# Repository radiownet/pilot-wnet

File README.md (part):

# Pilot Wnet

**An open studio controller for radio: arcade buttons and a joystick on an ESP32-S3 board designed to talk USB HID, Ethernet and Bluetooth LE (firmware not yet run on hardware) and to double as a LoRa 868 MHz mesh node (draft firmware variants).**

Polski: [README.pl.md](README.pl.md)

> [!WARNING]
> **Rev A is a prototype. DO NOT ORDER the Rev A board.**
> The layout has known defects (see [Known issues in Rev A](#known-issues-in-rev-a)) and needs a re-layout (Rev B) before anyone manufactures it.

> [!IMPORTANT]
> **AI-generated design, not reviewed by an engineer.** The Rev A schematic and PCB layout were generated by Python scripts (using SKiDL, Freerouting and a custom router) that AI agents (Claude) wrote and ran. ERC and DRC report 0 errors, but no hardware engineer has reviewed the design. See [How this project was made](#how-this-project-was-made).

*Render, **not a photograph**: the Rev A board has not been manufactured. An AI agent (Claude) made it in Blender (Cycles) from the KiCad files in this repository. The USB-C and RJ45 sockets and the tactile switches are approximate models, part markings are simplified, and parts marked DNP are not shown. More views: [top](docs/img/pilot-wnet-rev-a-render-top.jpg), [ESP32-S3 module close-up](docs/img/pilot-wnet-rev-a-render-esp32.jpg).*

## What is Pilot Wnet

Pilot Wnet is a physical controller for a radio studio. It was developed at the Polish radio station Radio Wnet (Radio Wnet Sp. z o.o.) and is published as open hardware. The operator presses big arcade buttons or moves a joystick; the controller sends authenticated state frames to the studio computer, where host software turns them into actions.

- **Controls:** six arcade buttons (four colour buttons, START and STOP) and a four-way arcade joystick in a wooden bartop-style cabinet; a Qwiic connector for an I2C OLED display.
- **Links to the studio computer (as designed):** USB HID, Ethernet (UDP) and Bluetooth LE. Wi-Fi is available but off by default. Every frame carries a CRC-16 and a truncated HMAC-SHA256 bound to a per-session nonce from the host. The frame and session protocol is documented in [docs/ESP32_PROTOKOL.md](docs/ESP32_PROTOKOL.md) (Polish).
- **Mesh node:** the same board carries an Ebyte E22-900M22S LoRa module (868 MHz) and can be flashed as a node for Meshtastic®- or MeshCore-based mesh networks (draft firmware variants, not built yet).

**There is no public host application.** Over USB the controller is a vendor-defined HID device (usage page `0xFF00`) that sends HMAC-authenticated frames, so you need your own host software to use it; the protocol document above is the reference. The host implementation (an application for the studio computer) is not public (yet); it currently reads USB HID and UDP, and BLE exists only in the firmware.

### Hardware at a glance (Rev A)

| Block | Rev A |
|---|---|
| Board | 90 × 100 mm, 4 layers (F.Cu signals, In1 GND, In2 +3V3, B.Cu signals), FR-4 1.6 mm, all parts on the top side, KiCad 10 |
| MCU | ESP32-S3-WROOM-1-N16R8 (16 MB flash, 8 MB octal PSRAM). The module is flush with the top edge; its PCB antenna lies over the board with a copper keep-out on all four layers (Espressif recommends the antenna beyond the edge or a cut-out; to be considered in Rev B) |
| Ethernet | WIZnet W5500 with a 25 MHz crystal, RJ45 HR911105A with integrated magnetics (the W5500 has no auto-MDIX) |
| Power | USB-C 5 V only (fuse, TVS, USBLC6), TI TLV62569 buck converter 5 V → 3.3 V; no battery in Rev A |
| LoRa | Ebyte E22-900M22S (SX1262, TCXO), 868 MHz, soldered by hand (not assembled by the factory), antenna through the module's IPEX connector |
| Inputs | 6 × JST XH 4-pin for buttons (J10–J15: signal, GND, LED+ 5 V, LED−), JST XH 5-pin for the joystick (J16); RC filters and SRV05-4 ESD arrays |
| Other | Qwiic for the OLED (J17) and for applications (J18), expansion header (J19), service UART (J20), RESET and BOOT buttons, status LED |
| Not assembled (DNP) | button backlight driver (PCA9685 + 6 × AO3400A), the E22 module, option resistors, USB capacitors, the buck converter feed-forward capacitor |
| Assembly | about 128 placed parts, 43 BOM lines with LCSC part numbers (JLCPCB assembly) |

Design decisions and their reasons: [DECYZJE.md](DECYZJE.md) (Polish, D1–D11). Some of its entries are out of date: the reason given for D7 ("solid ground") and the "Consequences" section (enclosure sized for the board) contradict the current files, see [docs/AUDYT_REV_A.md](docs/AUDYT_REV_A.md).

## Status

| Part | State |
|---|---|
| Schematic | generated from `pcb/obwod.py` by `pcb/schemat.py`; ERC 0 errors, 6 warnings (`lib_symbol_mismatch`: flattened derived symbols, no effect on connectivity) |
| PCB layout Rev A | DRC 0 errors, 0 unconnected items, 0 schematic-parity issues, 21 warnings (`lib_footprint_mismatch`: solder paste removed from DNP pads on purpose); **known layout defects, DO NOT ORDER** |
| Firmware (MicroPython) | written and tested in CPython against mocks; **never run on a real board** |
| Meshtastic / MeshCore variants | draft variant files, not built |
| Enclosure | parametric generators for cutting sheets and a 3D model; **does not match the Rev A board yet** (outline, USB-C/RJ45/SMA cut-outs, rear-wall pocket D8); some part dimensions are working values until real parts are measured |
| Circuit simulations | ngspice tests of the analogue sub-circuits (`sim/`); five expected failures document requirements that Rev A does not meet |
| Radio compliance (RED/CE) | **not assessed** |

ERC/DRC figures come from KiCad 10.0.8 on 20 November 2026 (`pcb/wyniki/erc.json`, `pcb/wyniki/drc.json`).

## Known issues in Rev A

An AI-agent audit (Claude agents, 20 Nov 2026, measurements taken from the board file; not reviewed by an engineer) found the defects below. They are the reason for Rev B: see the [Re-layout Rev B](.github/ISSUE_TEMPLATE/relayout-rev-b.md) task. The finding IDs refer to the audit summary in [docs/AUDYT_REV_A.md](docs/AUDYT_REV_A.md) (Polish, with an English summary).

1. **Inner planes carry signals** (layout-01, zasilanie-15). Most signals run on the inner layers (In1 GND, In2 +3V3), while B.Cu is almost empty. Under the W5500 the In1 ground covers only 39% of the package outline.
2. **Buck converter (U3, TLV62569) placed against the TI datasheet** (zasilanie-01, layout-02). The input capacitor is far from the IC, the SW node is long, and the FB trace runs under the SW node.
3. **25 MHz crystal (Y1): bad XO routing** (layout-04). The XO trace from the W5500 to Y1 makes a 17.6 mm detour through 4 vias (via R58 and C41) and runs on In2 directly under the crystal; LoRa SPI traces run on In1 under it. XI (5.1 mm) is fine.
4. **ESD protection far from the connectors** (zasilanie-02, interfejsy-04). For 6 of the 10 inputs the SRV05-4 channel is 46–66 mm (straight line) from its connector, because channels follow list order, not placement; the input traces are up to 93 mm long, mostly on In1.
5. **Ethernet pairs** (layout-05, interfejsy-05). The traces from the W5500 to the RJ45 are not routed as differential pairs over continuous ground: the halves of a pair run on different layers, with length mismatches of 11 mm and 4.6 mm.

Other open points (more in [docs/AUDYT_REV_A.md](docs/AUDYT_REV_A.md)):

- The crystal load capacitors (2 × 18 pF) are probably too small for a crystal with CL = 18 pF, so the oscillator may run fast (interfejsy-09). Simulation results and options: [sim/README.md](sim/README.md) (Polish).
- The W5500 reset RC has a small margin when 3V3 rises slowly (same file); the W5500 is reset only by this RC, not by the ESP32 (interfejsy-14).
- J19 (expansion) and J20 (service UART) are both 1 × 6 headers with **swapped power pins** (J19: pin 1 = +3V3, pin 2 = GND; J20: pin 1 = GND, pin 2 = +3V3). A UART adapter plugged into the wrong header swaps power and ground (interfejsy-03).
- **J20 does not match a standard 6-pin FTDI cable**: in either orientation the cable's VCC (+5 V) lands on EN or IO0 (interfejsy-02).
- **Pin 3 of every button connector J10–J15 always carries +5 V**, although the LED driver is not fitted; a miswired harness feeds 5 V through the SRV05-4 into the 3V3 rail (produkt-15, interfejsy-06).
- **D1 (SMF5.0A, breakdown 6.4–7.0 V) does not protect U3**, whose input is rated at 6 V maximum (zasilanie-04).
- USB D+/D− are not routed as a pair and the ESD path on D− is a stub (layout-06).
- The input of U7 (74LVC1G04) floats while the E22 module is not fitted (zasilanie-06, interfejsy-07).
- The USB-C footprint (J1) should be double-checked against the connector datasheet.
- The firmware uses MicroPython's built-in USB VID/PID; the project has no VID/PID of its own.

## How this project was made

Pilot Wnet is an experiment in agentic hardware design, and we label it as such.

- The circuit is described in Python with SKiDL 3.0 (`pcb/obwod.py`). A custom generator writes the KiCad schematic from it (`pcb/schemat.py`, net labels instead of wires).
- Placement, ground zones and net classes are scripted with KiCad's Python API (`pcb/plytka.py`). Routing was done with Freerouting 2.5.0, and the last connections were closed by a custom raster router (`pcb/v01/`).
- These scripts, the MicroPython firmware and its tests, the SPICE tests, the enclosure and Blender generators, the research reports (`research/`), the decision register, the ordering notes, the audit summary and this documentation were written by AI agents (Claude, by Anthropic) working under human direction. Decisions marked as defaults wait for approval by the project team.
- The result passes ERC and DRC with 0 errors. **No hardware engineer has reviewed the schematic or the layout yet**, and the audit above shows that 0 DRC errors does not make a good board.

For Rev B we want people to take over: a re-layout by a human designer, review by others, and automatic ERC/DRC checks on every change.

## Repository layout

| Path | Contents |
|---|---|
| `pcb/kicad/` | KiCad 10 project: schematic, board, design rules, netlist, library tables |
| `pcb/lib/` | project library (symbols and footprints; the E22 3D model is not included) |
| `pcb/*.py`, `pcb/v01/` | generator and check scripts: SKiDL circuit, schematic generator, placement, routing, fabrication export (notes in Polish: `pcb/README.md`, `pcb/v01/README_v01.md`) |
| `pcb/wyniki/` | ERC and DRC reports (JSON) |
| `firmware/micropython/` | controller firmware in MicroPython and its CPython tests (`testy/`) |
| `firmware/meshtastic/`, `firmware/meshcore/` | draft mesh-node variants (not built); `firmware/ci/build-mesh.yml` is an inactive draft workflow |
| `sim/` | ngspice tests of analogue sub-circuits, generated from `pcb/obwod.py` |
| `projekt/` | `arcade.toml` (enclosure and part dimensions; still assumes an older 100 × 100 mm board, see [Status](#status)) and the cutting-sheet generator (SVG for laser/CNC) |
| `blender/` | generator of the 3D model and renders of the cabinet (Blender batch mode; outputs and the top-panel artwork are not included) |
| `zamowienie/` | ordering notes for Rev A (reference only: do not order Rev A) |
| `research/` | research reports R1, R2, R3 and R5 (Polish, AI-written, sources with check dates; R4 is not included) |
| `docs/` | frame and session protocol (`ESP32_PROTOKOL.md`), hardware overview (`SPRZET.md`), audit summary (`AUDYT_REV_A.md`), all in Polish; renders of the Rev A board (`img/`) |
| `DECYZJE.md` | decision register D1–D11 (Polish) |
| `LICENSES/`, `REUSE.toml`, `NOTICE.md` | licence texts, per-file licensing (REUSE) and third-party notices |
| `.github/` | CI workflows, pull request and issue templates |

## Reproduce and verify

### ERC and DRC (KiCad 10)

The board and project files are saved with KiCad 10.0.8; the schematic is written by `pcb/schemat.py` in an older file format, which KiCad 10 opens and converts on save (expect a large one-time diff). From `pcb/kicad/`:

```sh
kicad-cli sch erc --severity-all --format json -o ../wyniki/erc.json pilot_wnet.kicad_sch
kicad-cli pcb drc --schematic-parity --refill-zones --severity-all --format json -o ../wyniki/drc.json pilot_wnet.kicad_pcb
```

Expected: 0 errors in both reports, 0 unconnected items, 0 schematic-parity issues, and the warnings listed under [Status](#status). CI runs the same checks in the official `kicad/kicad:10.0.8` Docker image on every push to main and every pull request ([.github/workflows/kicad.yml](.github/workflows/kicad.yml)) and keeps the reports as build artefacts. The gate is **0 errors, 0 unconnected items and 0 schematic-parity issues**; other warnings are checked in review.

Do not run "Update footprints from library" on the DNP parts: it restores the solder paste that was removed on purpose.

### Firmware tests (no hardware needed)

CPython 3.11 or newer, standard library only; MicroPython modules are replaced by mocks (`testy/atrapy.py`). Run each test file on its own, from `firmware/micropython/`:

```sh
for t in testy/test_*.py; do python -I -B -X utf8 "$t" || echo "FAILED: $t"; done
```

Windows (cmd): `for %f in (testy\test_*.py) do python -I -B -X utf8 %f`

The mocks show only that the code calls the APIs with the right pins and arguments. They do not show that USB HID, the W5500 or the SX1262 behave that way on a real board. A few tests are skipped on purpose: they document open findings. CI: [.github/workflows/firmware.yml](.github/workflows/firmware.yml).

### Circuit simulations (optional)

From `sim/`: `python -I -B -X utf8 -m unittest discover -s . -p "test_*.py"`. Without ngspice only the calculation and topology tests run. The SPICE tests need the ngspice console binary (set `PILOT_NGSPICE` to its path) and the `spicelib` package from PyPI, which brings NumPy and SciPy.

### Regenerating the board from scripts

The generator chain is published for transparency, but it is not a turnkey build yet. It needs KiCad 10's Python, SKiDL 3.0 and Freerouting 2.5.0 on a Java runtime, and parts of it still assume the original authors' setup. Re-running `pcb/plytka.py` overwrites manual copper edits.

### Dependencies

| Task | Needs |
|---|---|
| Firmware tests | CPython ≥ 3.11, standard library only |
| Firmware on the board | MicroPython for ESP32-S3 and the micropython-lib packages `usb-device-hid`, `aioble`, `lora-sync`, `lora-sx126x` (installed with `mpremote mip install`, see `firmware/README.md`) |
| ERC/DRC | KiCad 10 (`kicad-cli`) |
| Board generator (`pcb/`) | KiCad 10 Python (`pcbnew`), SKiDL 3.0, Freerouting 2.5.0 with a Java runtime, KiKit 1.8.1 (`pcb/fab.py`), NumPy (`pcb/v01/` router), PyMuPDF (`pcb/v01/opis_pdf.py`) |
| Simulations (`sim/`) | ngspice (console binary), `spicelib` (with NumPy, SciPy) |
| Enclosure (`projekt/`, `blender/`) | Python ≥ 3.11 (`tomllib`); Blender in batch mode for `blender/` |
| Licence check | `reuse` (REUSE tool) |

## Licences

| Scope | Licence |
|---|---|
| Hardware design: KiCad project and project library (`pcb/`), including the scripts that generate the design and their CSV/JSON data; enclosure and part geometry and the cutting-sheet generator (`projekt/`) | [CERN-OHL-S-2.0](LICENSES/CERN-OHL-S-2.0.txt) |
| Software: MicroPython firmware and tests (`firmware/micropython/`), MeshCore helper files (`firmware/meshcore/`), the draft mesh CI (`firmware/ci/`), simulations (`sim/`), the Blender generator (`blender/`), CI workflows | [MIT](LICENSES/MIT.txt) |
| Documentation: README files, `docs/`, `research/`, `DECYZJE.md`, `zamowienie/`, CONTRIBUTING, NOTICE, GitHub templates | [CC-BY-SA-4.0](LICENSES/CC-BY-SA-4.0.txt) |
| `.gitignore` files | [CC0-1.0](LICENSES/CC0-1.0.txt) |

Exceptions:

- `firmware/meshtastic/` is a derivative of the Meshtastic firmware and is licensed under the GPL ([GPL-3.0-only](LICENSES/GPL-3.0-only.txt)), like upstream.
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
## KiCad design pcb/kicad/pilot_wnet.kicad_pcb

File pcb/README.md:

# Pilot Wnet Rev A — płytka (KiCad 10, tor agentowy „kod → KiCad”)

> Projekt przygotował agent SI (Claude) w torze dla inżynierów pracujących agentowo. Każdy krok jest skryptem,
> a wynik to zwykły projekt KiCada 10, który człowiek otwiera i poprawia w GUI. Decyzje: `../DECYZJE.md`.
> Architektura i źródła liczb: `../research/R3_architektura_elektroniki.md` oraz wyciągi z kart producentów
> (workflow 18.10.2026: W5500 + HR911105A wg referencji WIZnet, ESP32-S3-WROOM-1 v1.8 + HDG, Ebyte E22,
> TI TLV62569, biblioteka JLCPCB).

## Tor narzędzi

| Krok | Skrypt | Narzędzie | Wynik |
|---|---|---|---|
| 1. Obwód (źródło prawdy) | `obwod.py` | SKiDL 3.0 | `kicad/pilot_wnet.net`, `kicad/bom_obwod.csv` |
| 2. Schemat | `schemat.py` | własny generator (etykiety sieci, bez przewodów) | `kicad/pilot_wnet.kicad_sch` — ERC: 0 błędów |
| 3. Płytka: obrys, rozmieszczenie, strefy GND, klasy sieci | `plytka.py uloz` | pcbnew (KiCad 10.0.1) | `kicad/pilot_wnet.kicad_pcb`, `.dsn` (plik pośredni, poza repozytorium) |
| 4. Trasowanie | `plytka.py trasuj` | Freerouting 2.5.0 (JAR, JRE 25, `-da`) | ścieżki z `.ses` (plik pośredni, poza repozytorium) |
| 5. Zgodność ze schematem, wykończenie | `plytka.py sciezki`, `plytka.py wykoncz` | pcbnew | ścieżki footprintów = UUID symboli; poszerzenie przewężeń, przelotki zszywające GND, reguły DRU |
| 6. DRC, panel KiKit, pliki JLCPCB, 3D (tor historyczny Rev A z 18.10 — niżej) | `fab.py` | kicad-cli, KiKit 1.8.1 | `wyniki/drc.json`, `kicad/pilot_wnet_panel.kicad_pcb` (poza repozytorium), `wyniki/jlcpcb/`, `wyniki/3d/` |

Kroki 1–6 to tor Rev A z 18.10.2026. Płytka w `kicad/` jest wersją v0.1 (zamówieniową): powstała z wyniku tego toru
dodatkowymi krokami z `v01/README_v01.md` (dotrasowanie, domknięcie, ręczne usunięcie wiszących przelotek, poprawki
opisu i poprawki przed zamówieniem). Panel KiKit 100 × 100 mm z kroku 6 jest torem historycznym (panel z 18.10 miał
starą trasę i nie jest częścią repozytorium) — pliki zamówienia v0.1 robią `v01/eksport_v01.py`
i `v01/pakiet_zamowienie_v01.py` (instrukcja: `../zamowienie/README.md`).

## Uruchamianie

Tor nie zależy od konkretnej maszyny. Potrzebne:

- KiCad 10 (Python KiCada z modułem `pcbnew` i `kicad-cli`); Rev A powstała w 10.0.1, poprawki przed zamówieniem v0.1
  (20.11) w 10.0.8;
- venv z dostępem do `pcbnew`: SKiDL 3.0 (`obwod.py`), KiKit 1.8.1 (tylko `fab.py`), easyeda2kicad (tylko do pobierania
  części z biblioteki EasyEDA/LCSC);
- do `plytka.py trasuj`: Java (JRE) 25 i Freerouting 2.5.0 jako JAR (tor Rev A z 18.10 wskazywał JRE jdk-25.0.4.1+1,
  dotrasowanie v0.1 z 19.11 użyło Temurin JRE 25.0.5+8).

Ścieżki narzędzi ustawiasz zmiennymi środowiskowymi:

| Zmienna | Skrypty | Domyślnie |
|---|---|---|
| `KICAD_CLI` | `cli.py`, `fab.py`, `v01/eksport_v01.py` | `C:\Program Files\KiCad\10.0\bin\kicad-cli.exe`; w `eksport_v01.py` instalacja dla użytkownika `%LOCALAPPDATA%\Programs\KiCad\10.0\bin\kicad-cli.exe` |
| `KICAD10_SYMBOL_DIR` | `obwod.py`, `schemat.py` | `C:\Program Files\KiCad\10.0\share\kicad\symbols` |
| `KICAD10_FOOTPRINT_DIR` | `obwod.py`, `plytka.py`, `sonda_fp.py` | `C:\Program Files\KiCad\10.0\share\kicad\footprints` |
| `KICAD10_3DMODEL_DIR` | KiCad (modele 3D footprintów z biblioteki KiCada); `eksport_v01.py` ustawia ją sam | — |
| `PILOT_JAVA` | `plytka.py trasuj` | `java` z `PATH` |
| `FREEROUTING` | `plytka.py trasuj` | `pcb/narzedzia/freerouting-2.5.0.jar` (katalog `narzedzia/` jest w `.gitignore`) |

Przy KiCadzie zainstalowanym gdzie indziej (instalacja dla użytkownika, Linux, macOS) ustaw zmienne KiCada jawnie.

**UWAGA: każdy krok łańcucha nadpisuje pliki w `kicad/`.** `obwod.py --wyjscie kicad` nadpisuje `pilot_wnet.net`
i `bom_obwod.csv`; `schemat.py` — `pilot_wnet.kicad_sch`, `piny_nc.json` i `sym-lib-table`; `plytka.py uloz`, `trasuj`,
`sciezki` i `wykoncz` — płytkę (`uloz` także `fp-lib-table`, `wykoncz` — `pilot_wnet.kicad_dru`). Uruchomienie łańcucha
w `kicad/` zniszczy płytkę v0.1 (zamówieniową), która powstała dodatkowym torem z `v01/README_v01.md`. Do eksperymentów
używaj osobnego katalogu **obok `lib/`** (np. `kicad_proba/`, jest w `.gitignore`): tabele bibliotek i model 3D E22
wskazują `${KIPRJMOD}/../lib`, a `plytka.py uloz` czyta `piny_nc.json` z katalogu wyjściowego i bez niego DRC zgłosi
niezgodność ze schematem. `schemat.py --wyjscie` przyjmuje ścieżkę pliku, nie katalogu.

Z katalogu `pcb/`, Pythonem KiCada (venv jak wyżej):

```bash
python obwod.py --wyjscie kicad_proba && python schemat.py --netlista kicad_proba/pilot_wnet.net --wyjscie kicad_proba/pilot_wnet.kicad_sch && python plytka.py uloz --netlista kicad_proba/pilot_wnet.net --wyjscie kicad_proba && python plytka.py trasuj --wyjscie kicad_proba --przebiegi 15 && python plytka.py sciezki --wyjscie kicad_proba && python plytka.py wykoncz --wyjscie kicad_proba
```

`fab.py` nie ma parametrów i działa zawsze na `kicad/`: nadpisuje `wyniki/drc.json` (raport płytki v0.1 w repozytorium)
i tworzy panel `kicad/pilot_wnet_panel.*` (w `.gitignore`). Freerouting z `-mt 8` nie jest deterministyczny, więc łańcuch
nie odtworzy płytki bajt w bajt; stanem odniesienia jest `kicad/pilot_wnet.kicad_pcb` w tym repozytorium.

Model 3D modułu E22 (`lib/pilot_jlc.3dshapes/WIRELM-SMD_L20.0-W14.0-H3.0-E22-900M22S.step`, z biblioteki EasyEDA/LCSC
przez easyeda2kicad) **nie jest dołączony** — jego licencja jest nieustalona. Footprint i płytka nadal go wskazują, więc
podgląd 3D, rendery i eksport STEP/GLB (`fab.py`) pokażą moduł E22 bez bryły (KiCad może zgłosić brak modelu); miedzi,
Gerberów ani BOM to nie zmienia.

## Płytka

- 90 × 100 mm, 4 warstwy (In1 GND, In2 +3V3), FR-4 1,6 mm; w torze Rev A z 18.10 panel 100 × 100 mm z listwami 5 mm po bokach (KiKit, `fab.py`) — tor historyczny, zamówienie v0.1: `v01/eksport_v01.py` i `../zamowienie/README.md`.
- Tylna krawędź (y = 0) przy tylnej ściance obudowy: USB-C (J1), RJ45 z transformatorem (J2), antena PCB modułu ESP32-S3-WROOM-1 (strefa bez miedzi z footprintu), dioda stanu D2.
- Przednia krawędź: złącza 6 przycisków JST XH 4-pin (J10–J15: 1 sygnał, 2 GND, 3 LED+ 5 V, 4 LED−); lewa: joystick XH 5-pin (J16: 1 GND, 2 góra, 3 dół, 4 lewo, 5 prawo). Prawa: Qwiic OLED (J17) i Qwiic aplikacji (J18), rozszerzenia (J19), serwis UART (J20), RESET i BOOT.
- Przydział GPIO: tabela w `obwod.py` i `../firmware/micropython/lib/konfig_plytki.py` (zgodne, sprawdzone przez recenzenta firmware).
- Bez montażu (DNP): tor podświetlenia (PCA9685, 6 × AO3400A — D1), moduł E22 (lutowany ręcznie — D4), rezystory opcji, kondensatory USB, feed-forward przetwornicy.

## Znane ograniczenia i decyzje techniczne

- **schematizer 0.2.0** (SKiDL) zwierał sieci (ERC: +3V3 z GND) i zapisywał symbol HR911105A nieczytelny dla KiCada 10.0.1 — zastąpiony `schemat.py`.
- **Freerouting CLI 2.5.0 (natywny)** wywraca się w pętli trasowania (GraalVM: brak konfiguracji serializacji `ComponentOutline`) i wisi — używamy JAR na JRE 25.
- Footprint WROOM-1 ma zawężony obrys montażowy (biblioteczny obejmował 15 mm wokół anteny; strefę RF pilnuje strefa bez miedzi) i przelotki termiczne 0,3 mm (min. JLCPCB dla 2 warstw) — stąd ostrzeżenie `lib_footprint_mismatch`.
- Symbol E22 z easyeda2kicad (C411293) ma ręcznie nadane typy pinów wg karty Ebyte.
- Antena LoRa przez złącze IPEX na module (bez ścieżki RF 50 Ω na płytce bez kontroli impedancji).
- Ostrzeżenia ERC `lib_symbol_mismatch` (AO3400A, TLV62569): spłaszczone symbole dziedziczące, bez wpływu na połączenia.

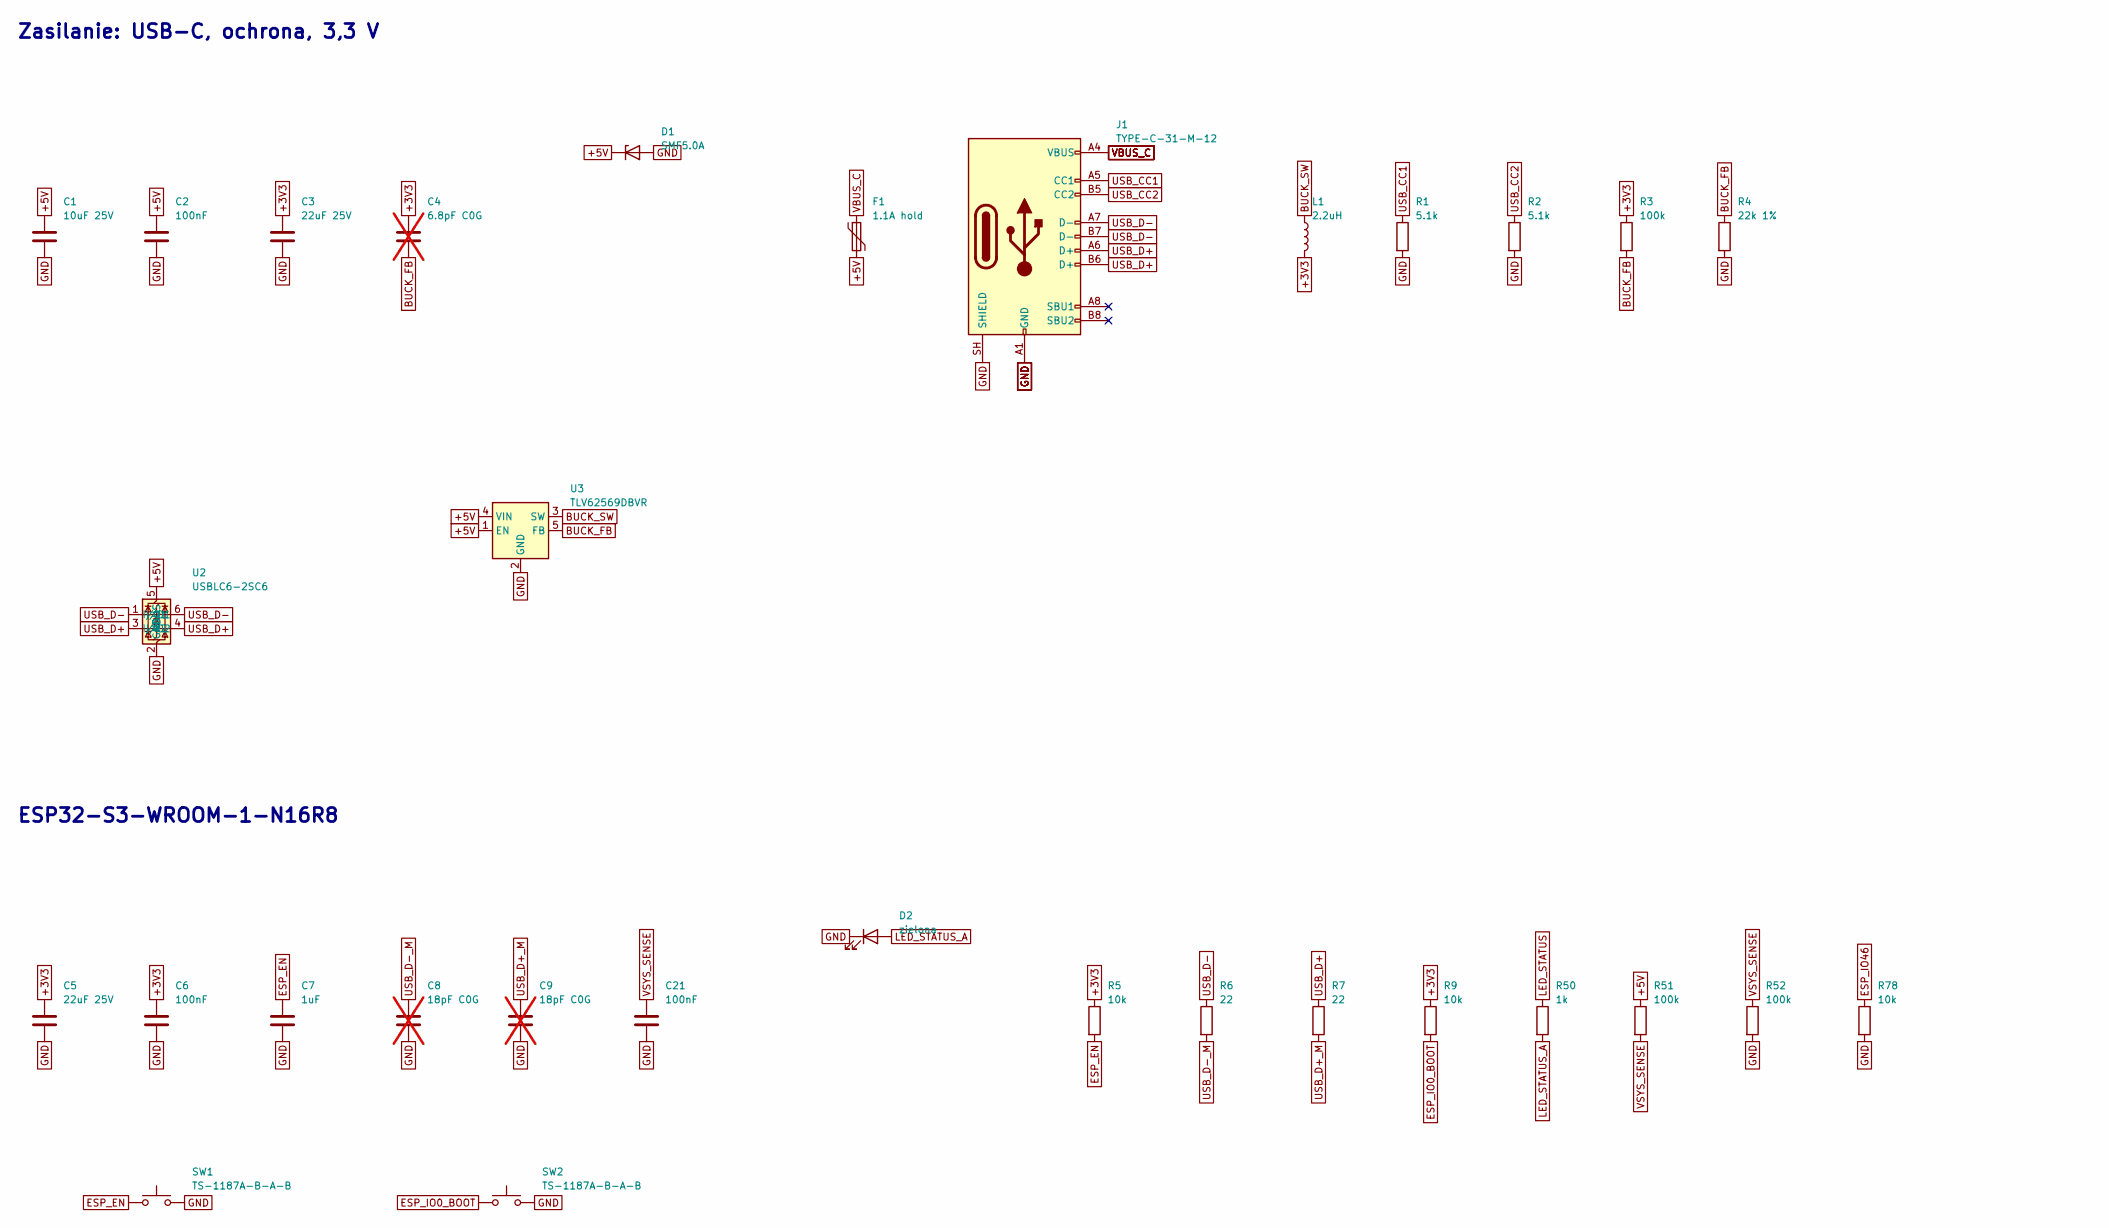
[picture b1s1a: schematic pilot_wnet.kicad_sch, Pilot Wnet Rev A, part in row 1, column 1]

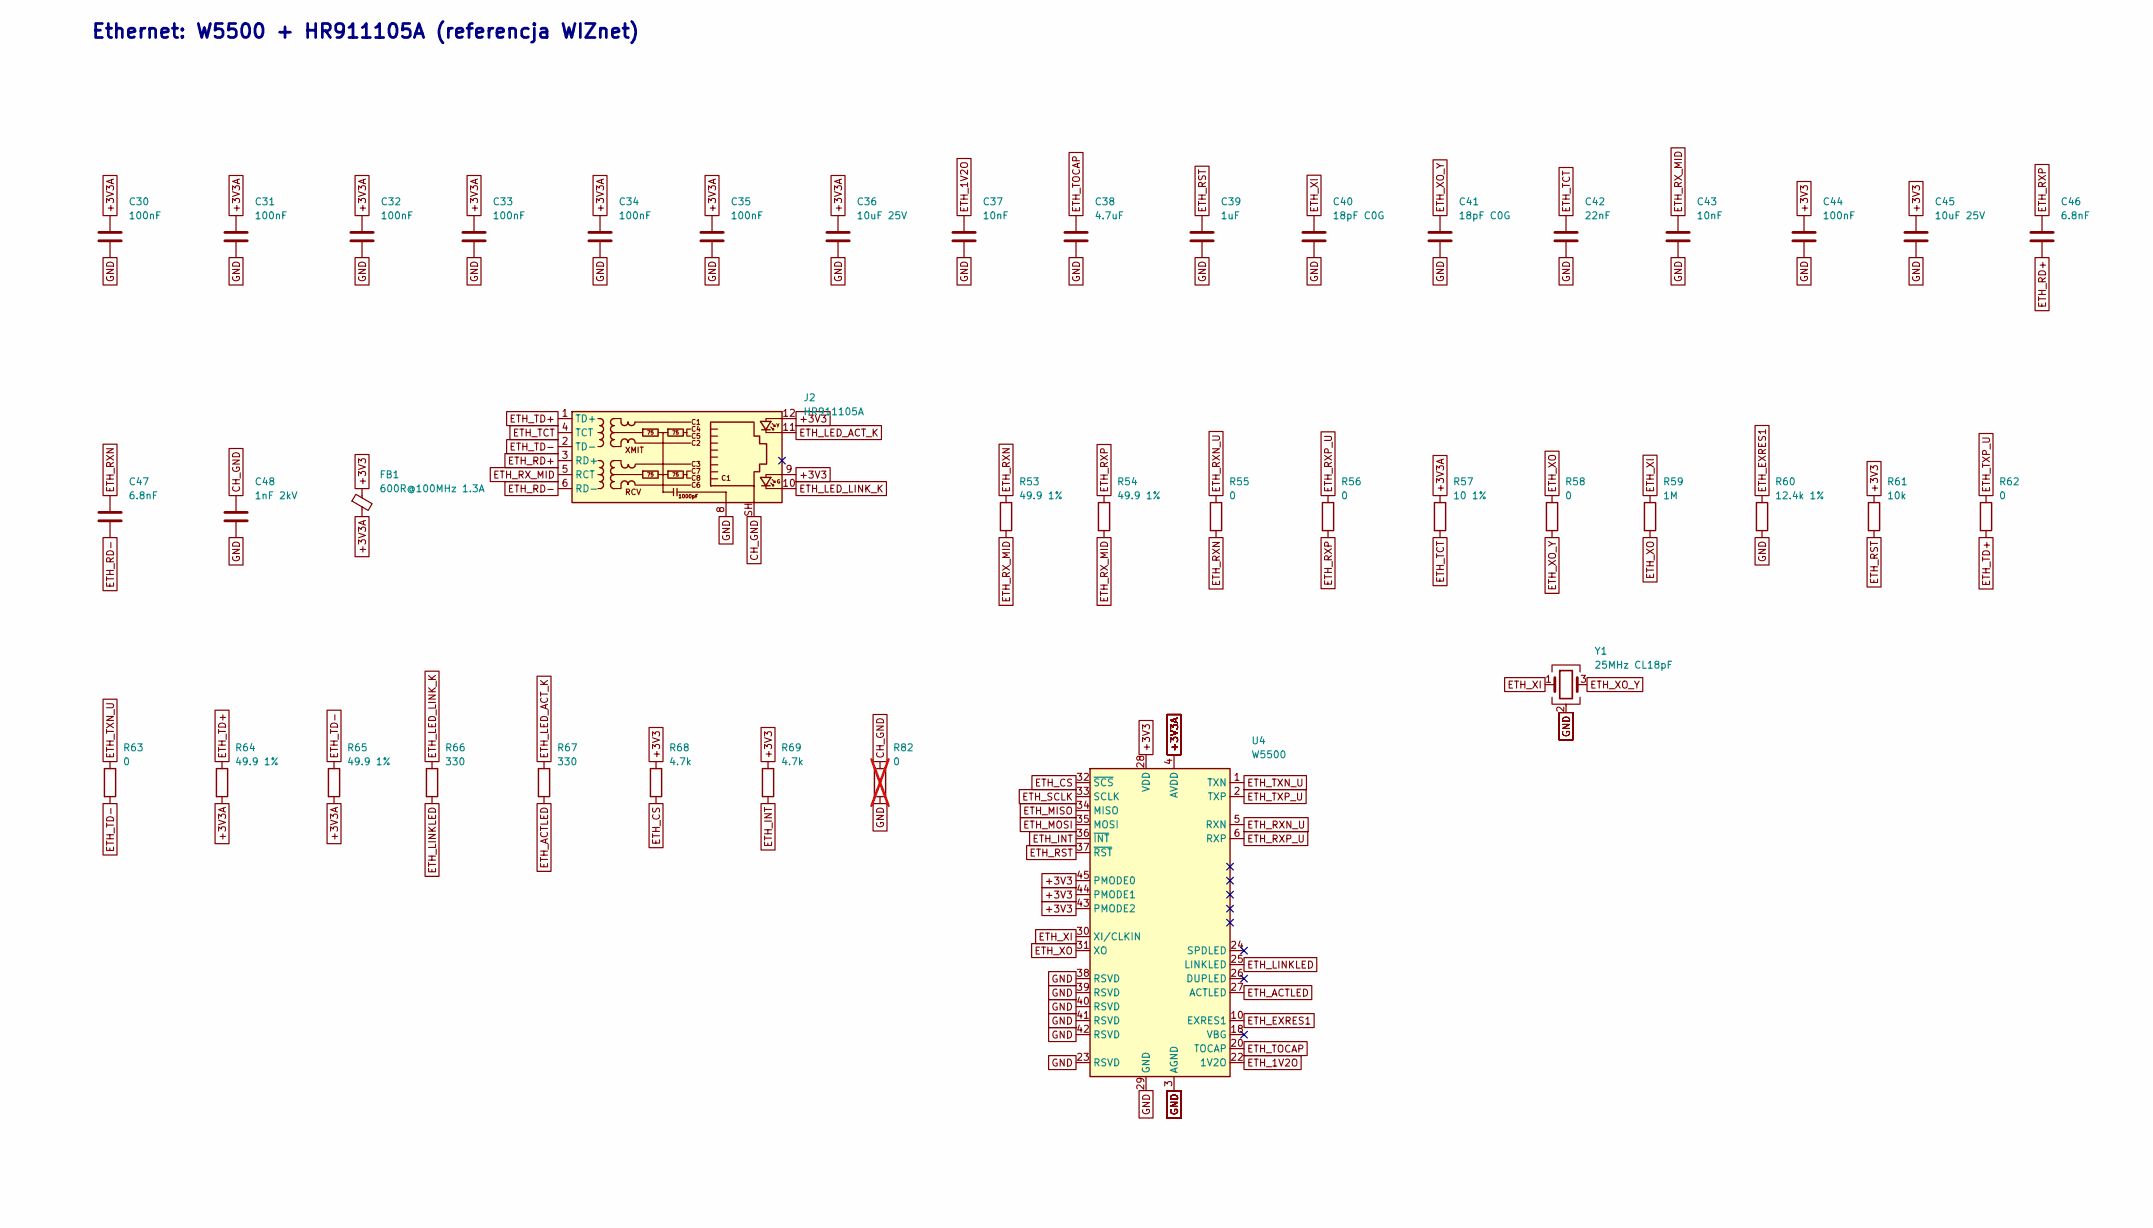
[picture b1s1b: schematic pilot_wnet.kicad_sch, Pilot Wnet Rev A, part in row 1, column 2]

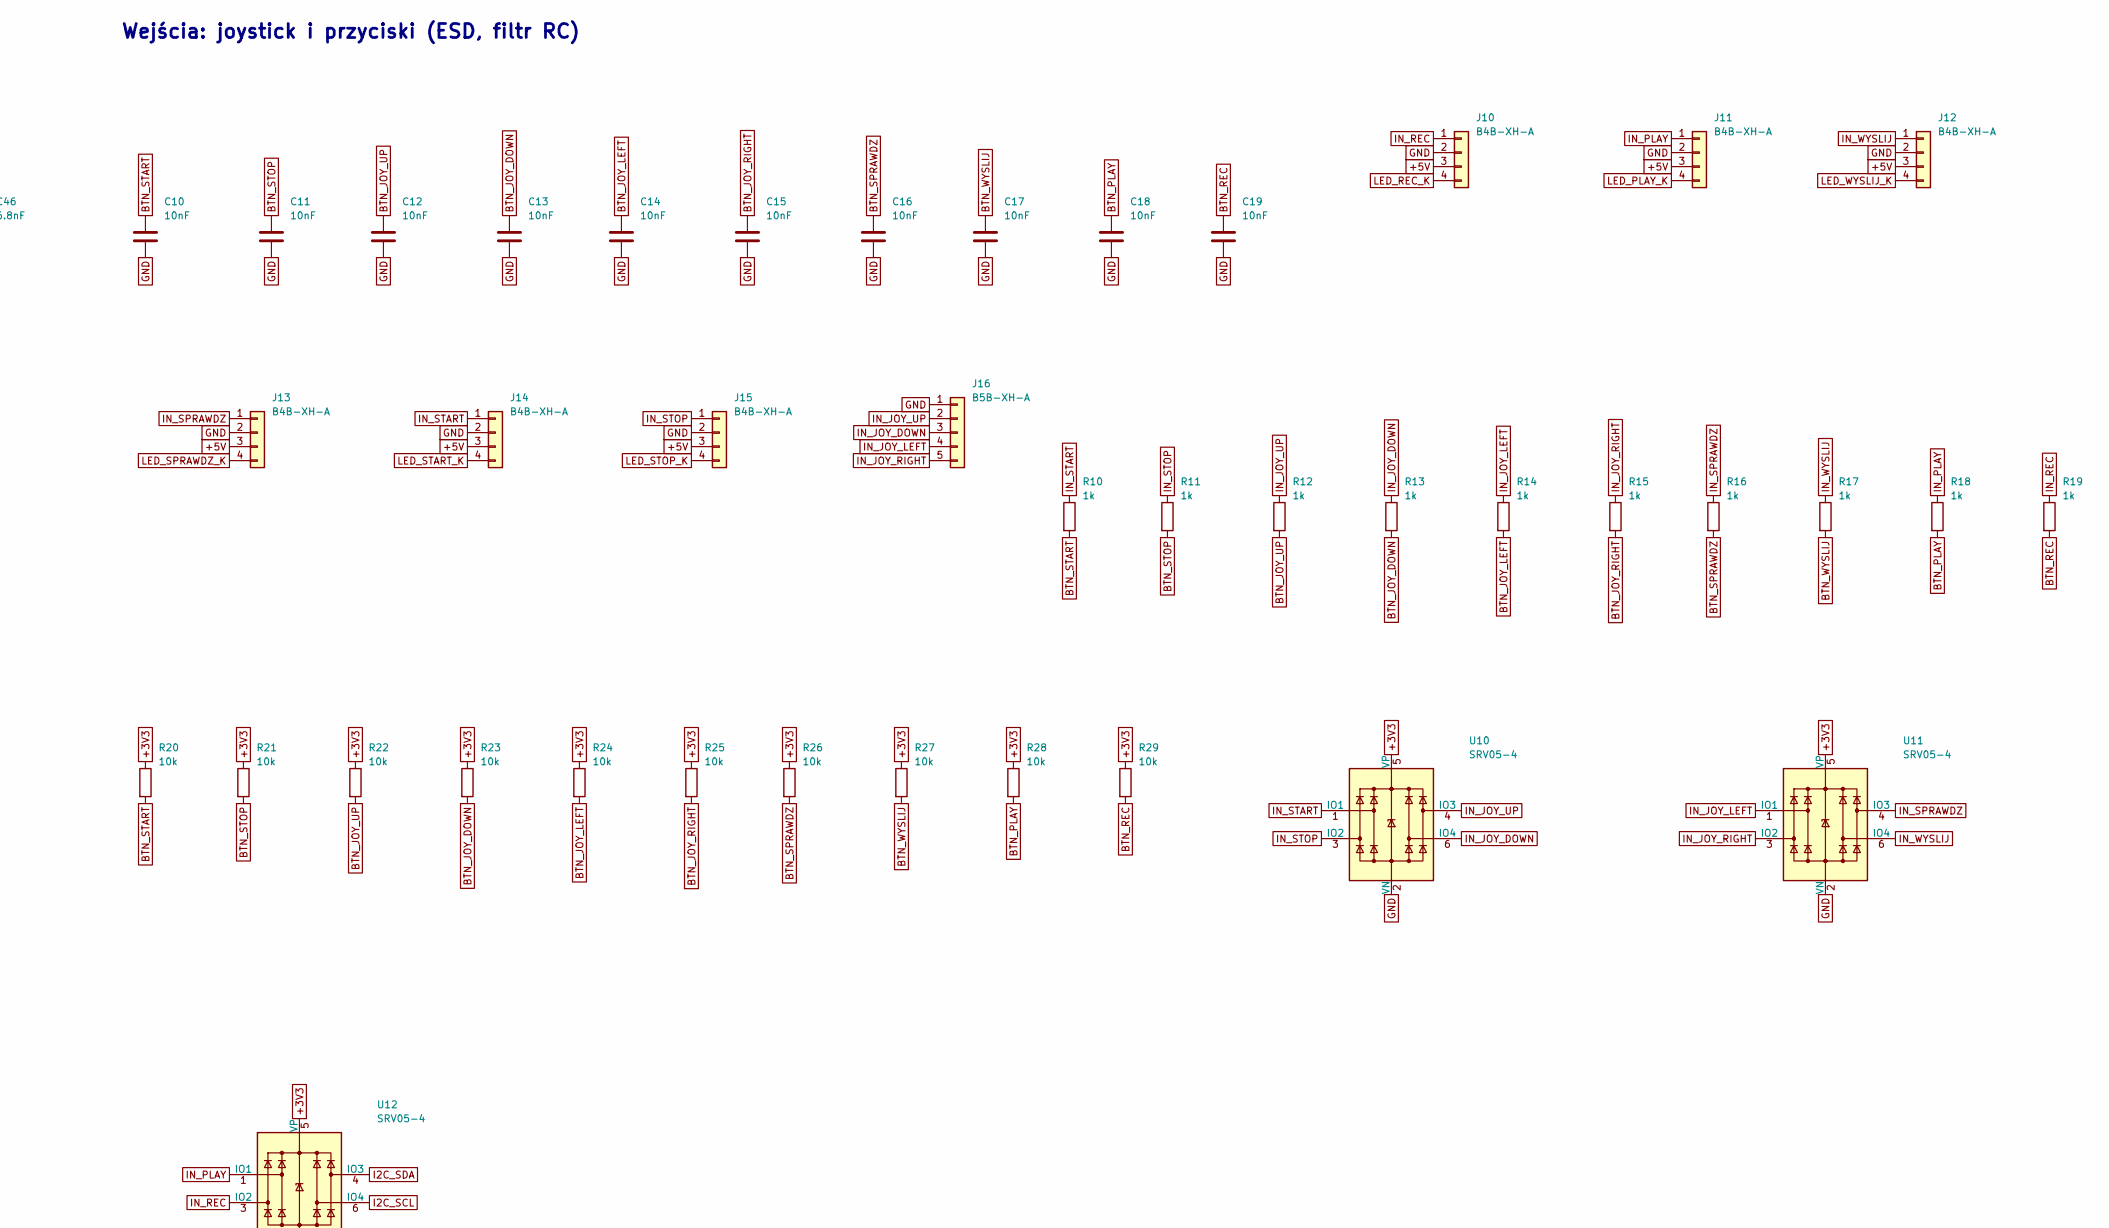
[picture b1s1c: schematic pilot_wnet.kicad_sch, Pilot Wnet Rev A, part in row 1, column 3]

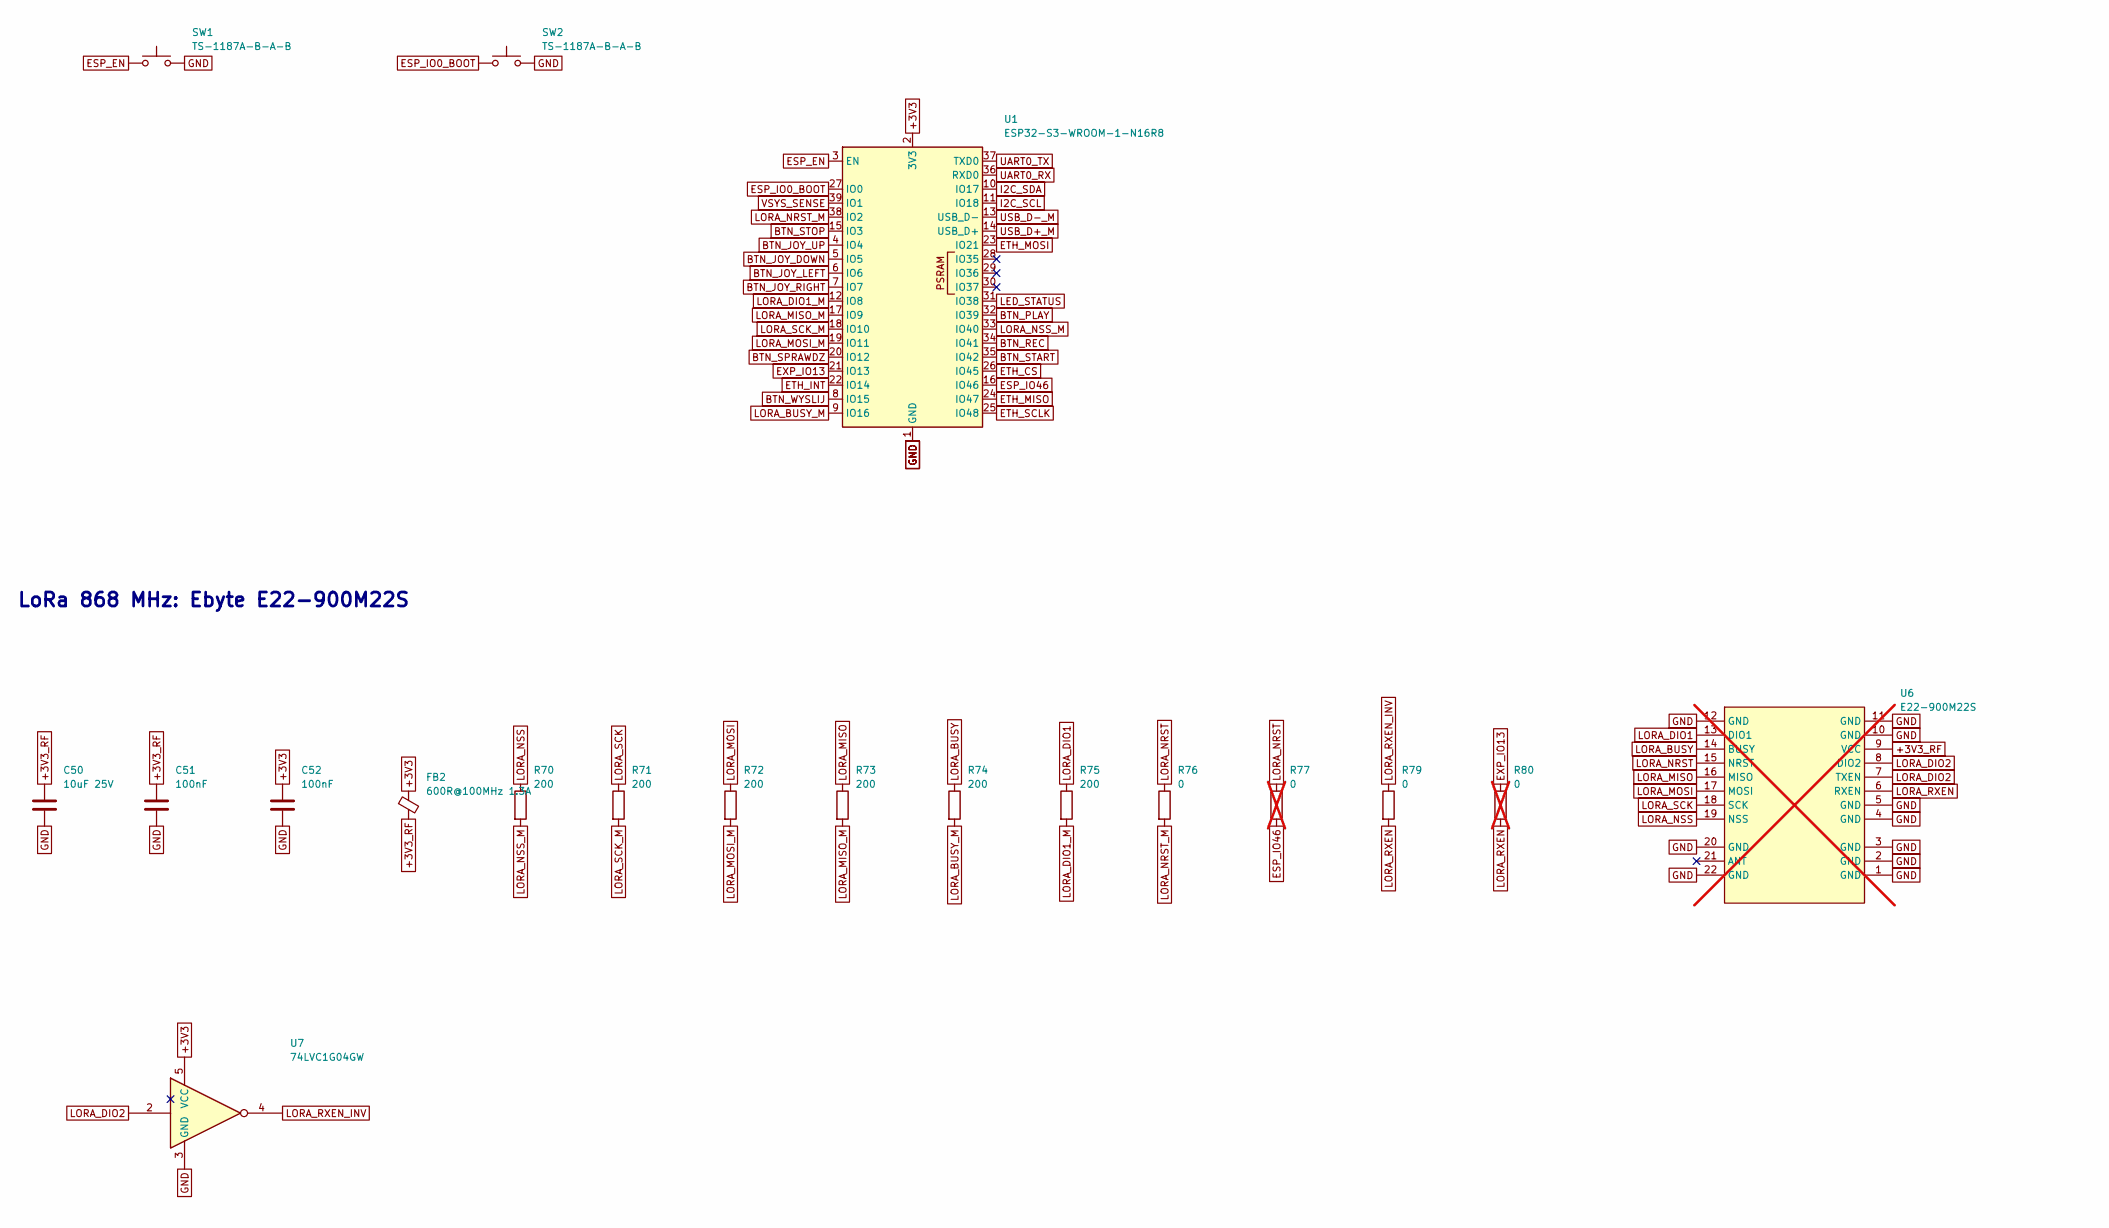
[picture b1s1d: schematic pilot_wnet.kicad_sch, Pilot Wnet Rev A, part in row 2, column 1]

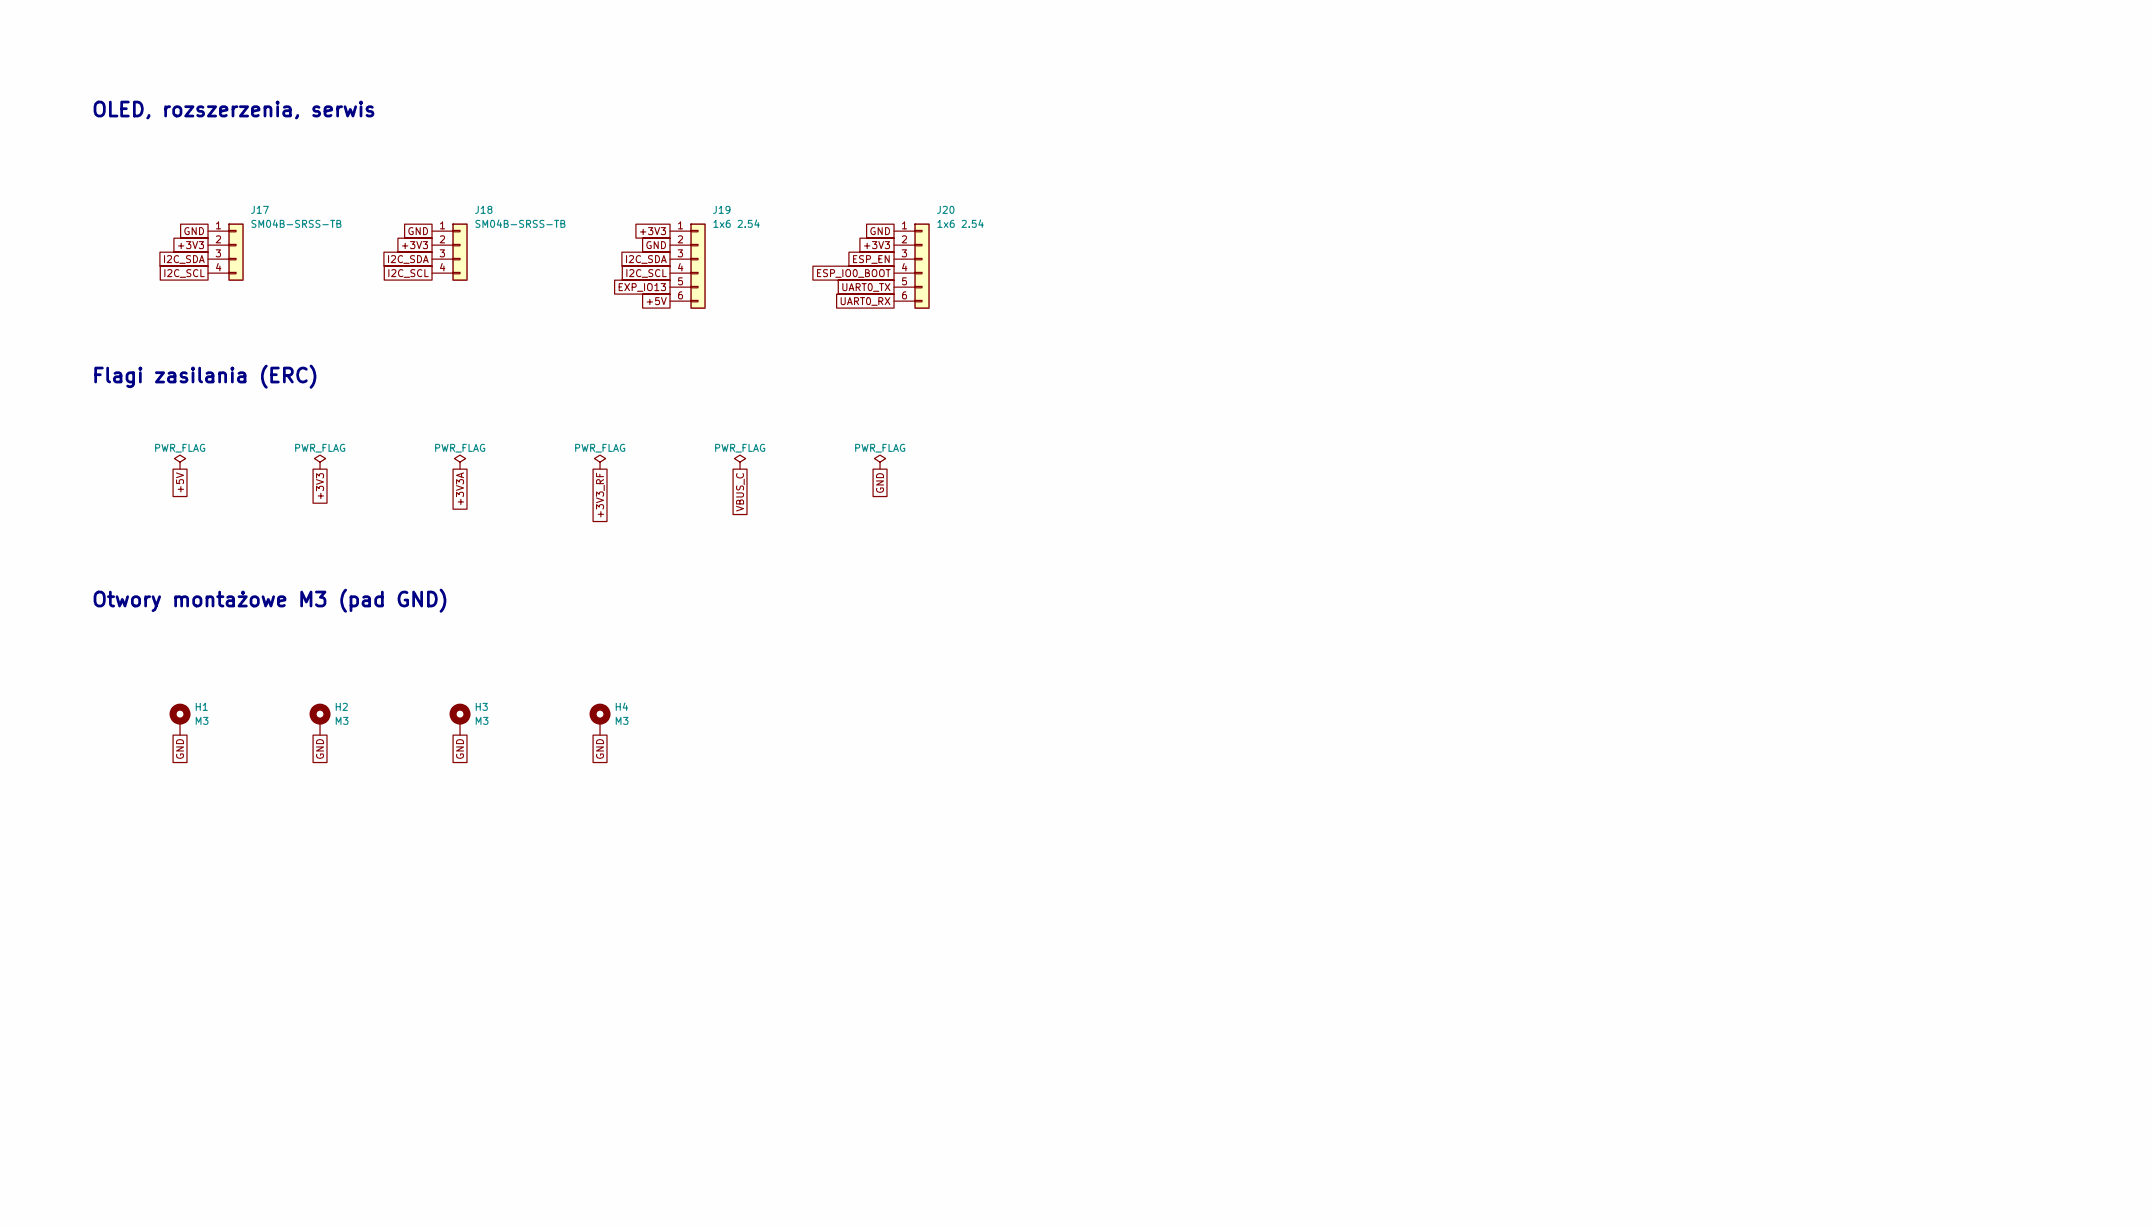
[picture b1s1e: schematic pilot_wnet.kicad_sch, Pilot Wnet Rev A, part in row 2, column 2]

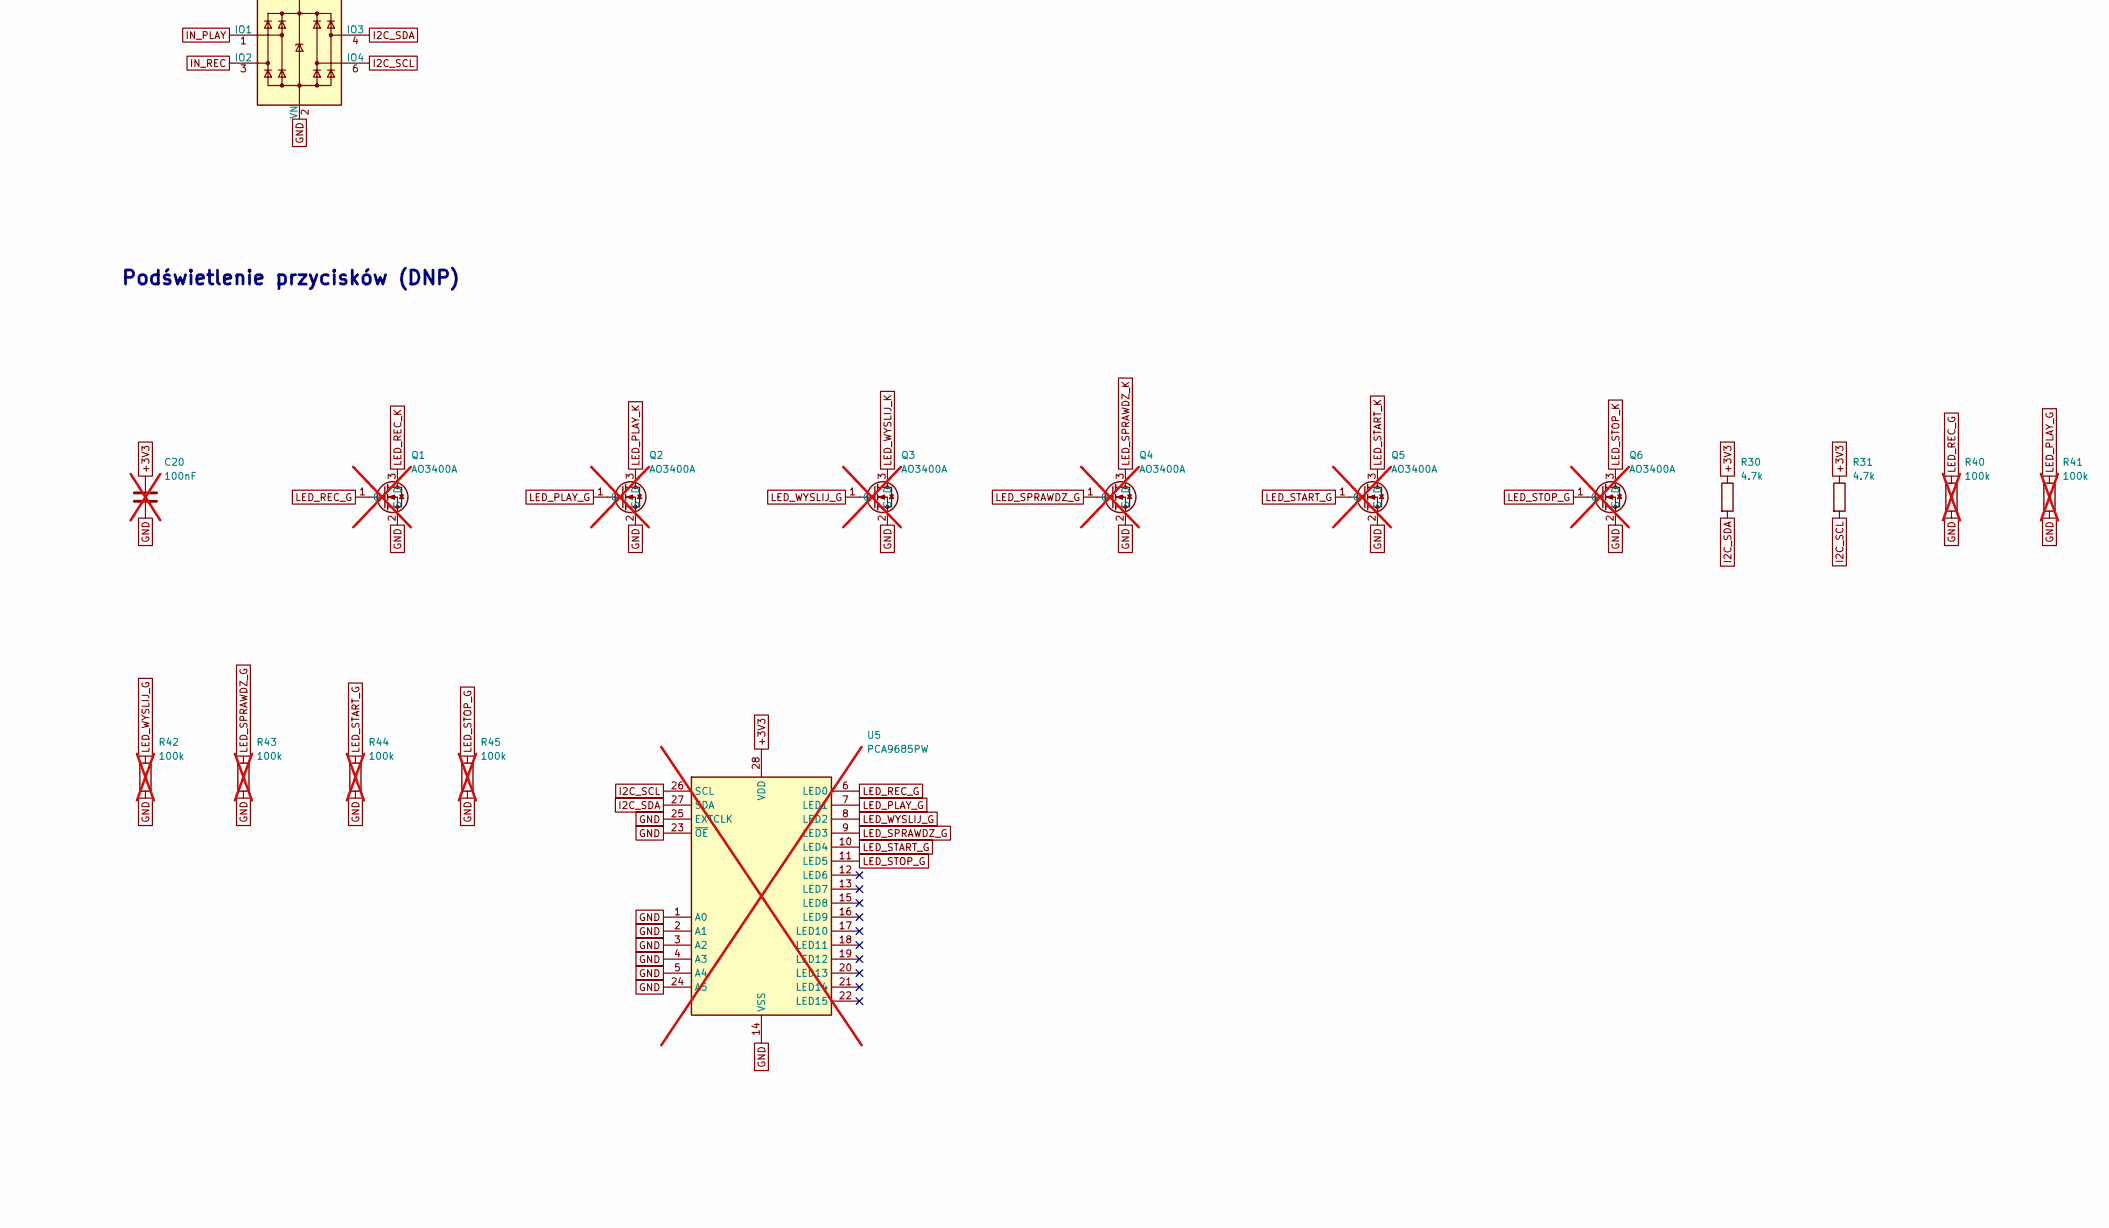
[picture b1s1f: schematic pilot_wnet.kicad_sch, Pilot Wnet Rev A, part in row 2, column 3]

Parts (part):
C1, C36, C45, C50: 10uF 25V; C_0805_2012Metric; LCSC C15850
C2, C6, C21, C30, C31, C32, C33, C34, C35, C44, C51, C52: 100nF; C_0402_1005Metric; LCSC C1525
C3, C5: 22uF 25V; C_0805_2012Metric; LCSC C45783
C4: 6.8pF C0G; C_0402_1005Metric; LCSC C237286; not fitted
C7, C39: 1uF; C_0402_1005Metric; LCSC C52923
C8, C9: 18pF C0G; C_0402_1005Metric; LCSC C1549; not fitted
C10, C11, C12, C13, C14, C15, C16, C17, C18, C19, C37, C43: 10nF; C_0402_1005Metric; LCSC C15195
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
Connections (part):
+3V3: C3.1, C4.1, C5.1, C6.1, C20.1, C44.1, C45.1, C52.1, FB1.1, FB2.1, J2.9, J2.12, J17.2, J18.2, J19.1, J20.2, L1.2, R3.1, R5.1, R9.1, R20.1, R21.1, R22.1, R23.1, R24.1, R25.1, R26.1, R27.1, R28.1, R29.1, R30.1, R31.1, R61.1, R68.1, R69.1, U1.2 (3V3), U4.28 (VDD), U4.43 (PMODE2), U4.44 (PMODE1), U4.45 (PMODE0), U5.28 (VDD), U7.5 (VCC), U10.5 (VP), U11.5 (VP), U12.5 (VP)
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
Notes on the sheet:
Zasilanie: USB-C, ochrona, 3,3 V
ESP32-S3-WROOM-1-N16R8
LoRa 868 MHz: Ebyte E22-900M22S
Ethernet: W5500 + HR911105A (referencja WIZnet)
OLED, rozszerzenia, serwis
Wejścia: joystick i przyciski (ESD, filtr RC)
Podświetlenie przycisków (DNP)
Flagi zasilania (ERC)
Otwory montażowe M3 (pad GND)

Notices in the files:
README.md:
- `pcb/lib/pilot_jlc.pretty/ESP32-S3-WROOM-1_Pilot.kicad_mod` and `USB_C_Receptacle_HRO_TYPE-C-31-M-12_Pilot.kicad_mod` are modified footprints from the KiCad libraries: CC-BY-SA-4.0 with the [KiCad libraries exception](LICENSES/KiCad-libraries-exception.txt).
CERN-OHL-S is strongly reciprocal: if you convey (sell or give away) hardware made from a modified design, or the modified design itself, you must make the complete source available to the recipients under the same licence.
Source Location (CERN-OHL-S, section 4): . Rev A does not carry it on the silkscreen yet; Rev B will.
